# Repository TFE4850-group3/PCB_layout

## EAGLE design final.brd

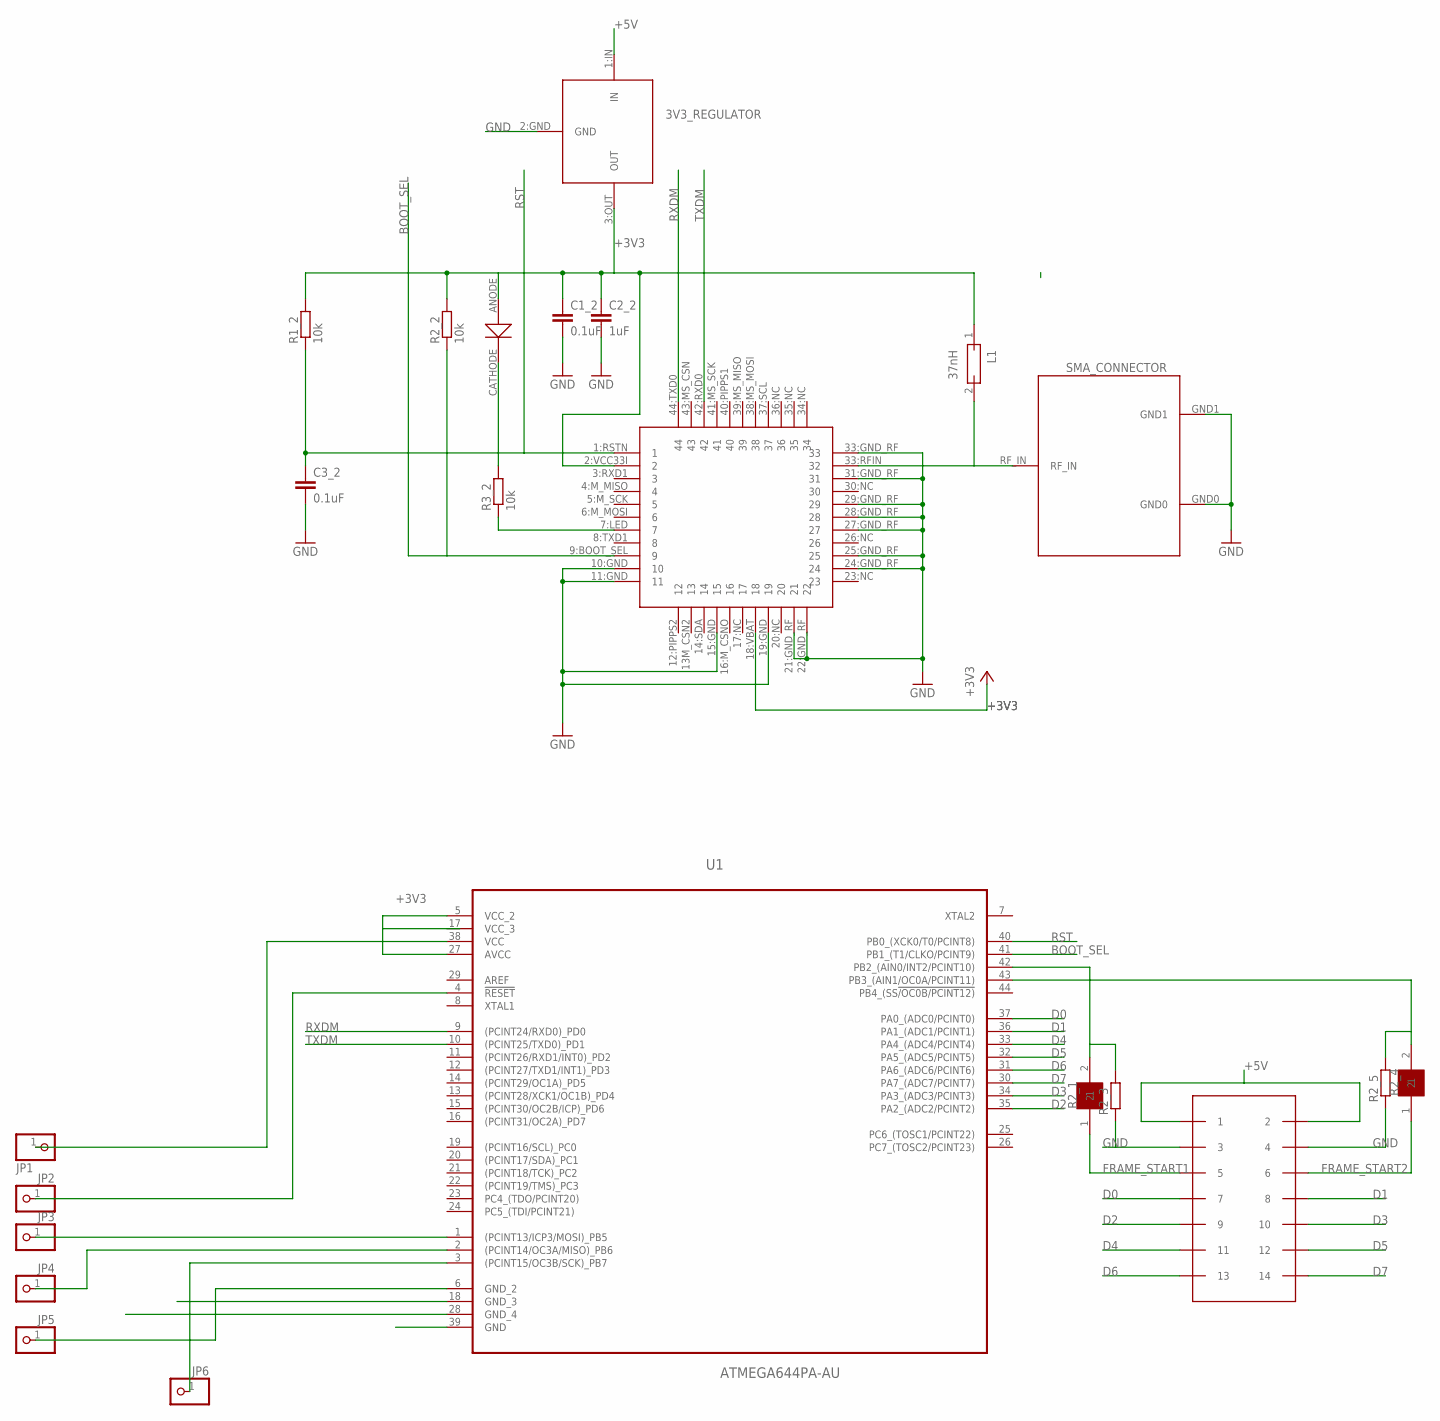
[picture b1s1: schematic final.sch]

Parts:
3V3_REGULATOR: LM3940IT-3.3/NOPB; 3PIN
C1_2, C3_2: 0.1uF; C0402
C2_2: 1uF; C0402
GPS_1: VENUS838FLPX; LGA-44
HARWIN_CONNECTOR: HARWIN_CONNECTOR; 14DIP
JP1, JP2, JP3, JP4, JP5, JP6: PINHD-1X1; 1X01
L1: 37nH; 0805
R1_2, R2_2, R3_2: 10k; R0402
R2_1, R2_4: 0805RESISTOR; 0805
R2_3, R2_5: R-EU_R0402; R0402
SMA_CONNECTOR: SMA_SIDE
U1: ATMEGA644PA-AU; QFP80P1200X1200X120-44N
U$1: HSMH-C190-DIODE

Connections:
+3V3: 3V3_REGULATOR.3:OUT (OUT), C1_2.1, C2_2.1, GPS_1.2:VCC33I (2), GPS_1.18:VBAT (18), JP1.1, L1.1, R1_2.2, R2_2.2, U1.5 (VCC_2), U1.17 (VCC_3), U1.27 (AVCC), U1.38 (VCC), U$1.ANODE (AN)
+5V: 3V3_REGULATOR.1:IN (IN), HARWIN_CONNECTOR.1, HARWIN_CONNECTOR.2
BOOT_SEL: GPS_1.9:BOOT_SEL (9), R2_2.1, U1.41 (PB1_(T1/CLKO/PCINT9))
D0: HARWIN_CONNECTOR.7, U1.37 (PA0_(ADC0/PCINT0))
D1: HARWIN_CONNECTOR.8, U1.36 (PA1_(ADC1/PCINT1))
D2: HARWIN_CONNECTOR.9, U1.35 (PA2_(ADC2/PCINT2))
D3: HARWIN_CONNECTOR.10, U1.34 (PA3_(ADC3/PCINT3))
D4: HARWIN_CONNECTOR.11, U1.33 (PA4_(ADC4/PCINT4))
D5: HARWIN_CONNECTOR.12, U1.32 (PA5_(ADC5/PCINT5))
D6: HARWIN_CONNECTOR.13, U1.31 (PA6_(ADC6/PCINT6))
D7: HARWIN_CONNECTOR.14, U1.30 (PA7_(ADC7/PCINT7))
FRAME_START1: HARWIN_CONNECTOR.5, R2_1.1
FRAME_START2: HARWIN_CONNECTOR.6, R2_4.1
GND: 3V3_REGULATOR.2:GND (GND), C1_2.2, C2_2.2, C3_2.2, GPS_1.10:GND (10), GPS_1.11:GND (11), GPS_1.15:GND (15), GPS_1.19:GND (19), GPS_1.21:GND_RF (21), GPS_1.22:GND_RF (22), GPS_1.24:GND_RF (24), GPS_1.25:GND_RF (25), GPS_1.27:GND_RF (27), GPS_1.28:GND_RF (28), GPS_1.29:GND_RF (29), GPS_1.31:GND_RF (31), GPS_1.33:GND_RF (33), HARWIN_CONNECTOR.3, HARWIN_CONNECTOR.4, JP5.1, R2_3.1, R2_5.1, SMA_CONNECTOR.GND0, SMA_CONNECTOR.GND1, U1.6 (GND_2), U1.18 (GND_3), U1.28 (GND_4), U1.39 (GND)
MISO: JP4.1, U1.2 ((PCINT14/OC3A/MISO)_PB6)
MOSI: JP3.1, U1.1 ((PCINT13/ICP3/MOSI)_PB5)
unnamed: R3_2.2, U$1.CATHODE (CATH)
unnamed: GPS_1.7:LED (7), R3_2.1
unnamed: R2_1.2, R2_3.2, U1.42 (PB2_(AIN0/INT2/PCINT10))
unnamed: R2_4.2, R2_5.2, U1.43 (PB3_(AIN1/OC0A/PCINT11))
RESET: JP2.1, U1.4 (!RESET)
RFIN_2: GPS_1.33:RFIN (32), L1.2, SMA_CONNECTOR.RF_IN
RST: C3_2.1, GPS_1.1:RSTN (1), R1_2.1, U1.40 (PB0_(XCK0/T0/PCINT8))
RXDM: GPS_1.44:TXD0 (44), U1.9 ((PCINT24/RXD0)_PD0)
SCK: JP6.1, U1.3 ((PCINT15/OC3B/SCK)_PB7)
TXDM: GPS_1.42:RXD0 (42), U1.10 ((PCINT25/TXD0)_PD1)

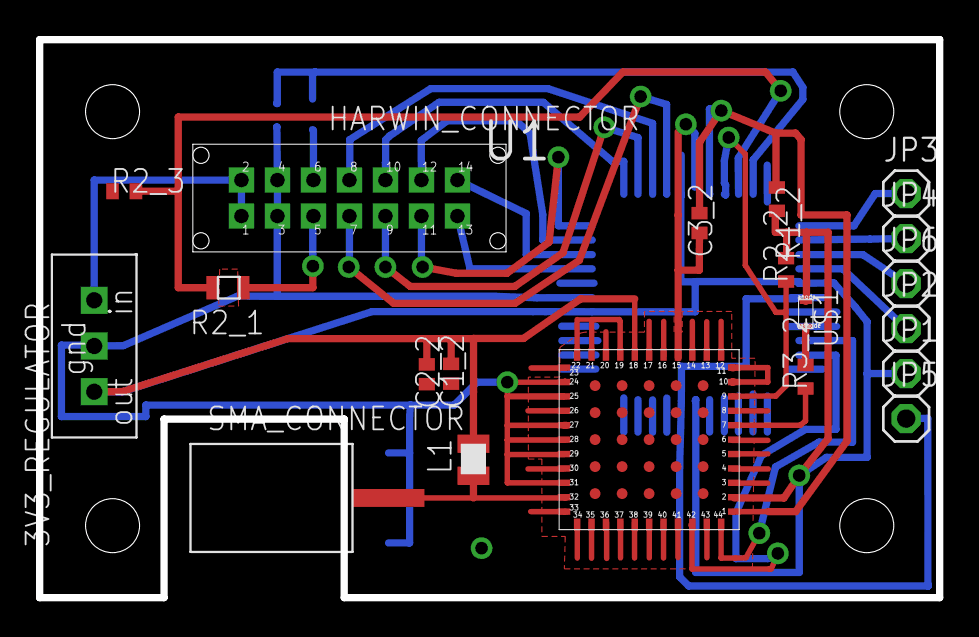
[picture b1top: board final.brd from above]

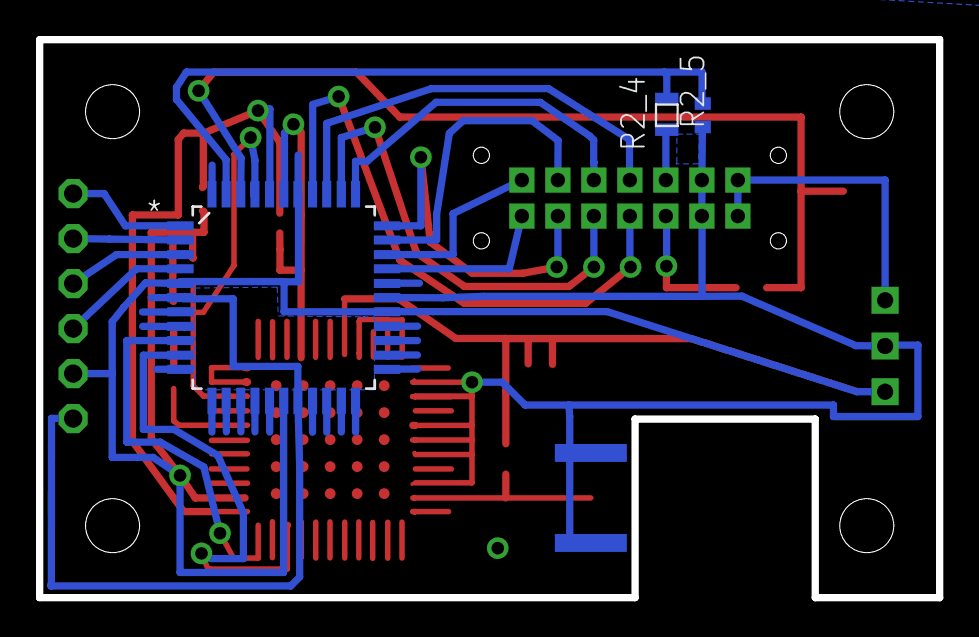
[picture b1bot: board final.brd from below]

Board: 2 copper layers, 50.0 x 31.0 mm, 23 parts (3 on the bottom side), 26 nets.

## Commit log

2016-05-04 final
